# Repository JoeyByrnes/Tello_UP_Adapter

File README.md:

# Tello_UP_Adapter
hardware design files for UP Xtreme port adapter for Tello Robot

<br>

<br>

<br>

<br>

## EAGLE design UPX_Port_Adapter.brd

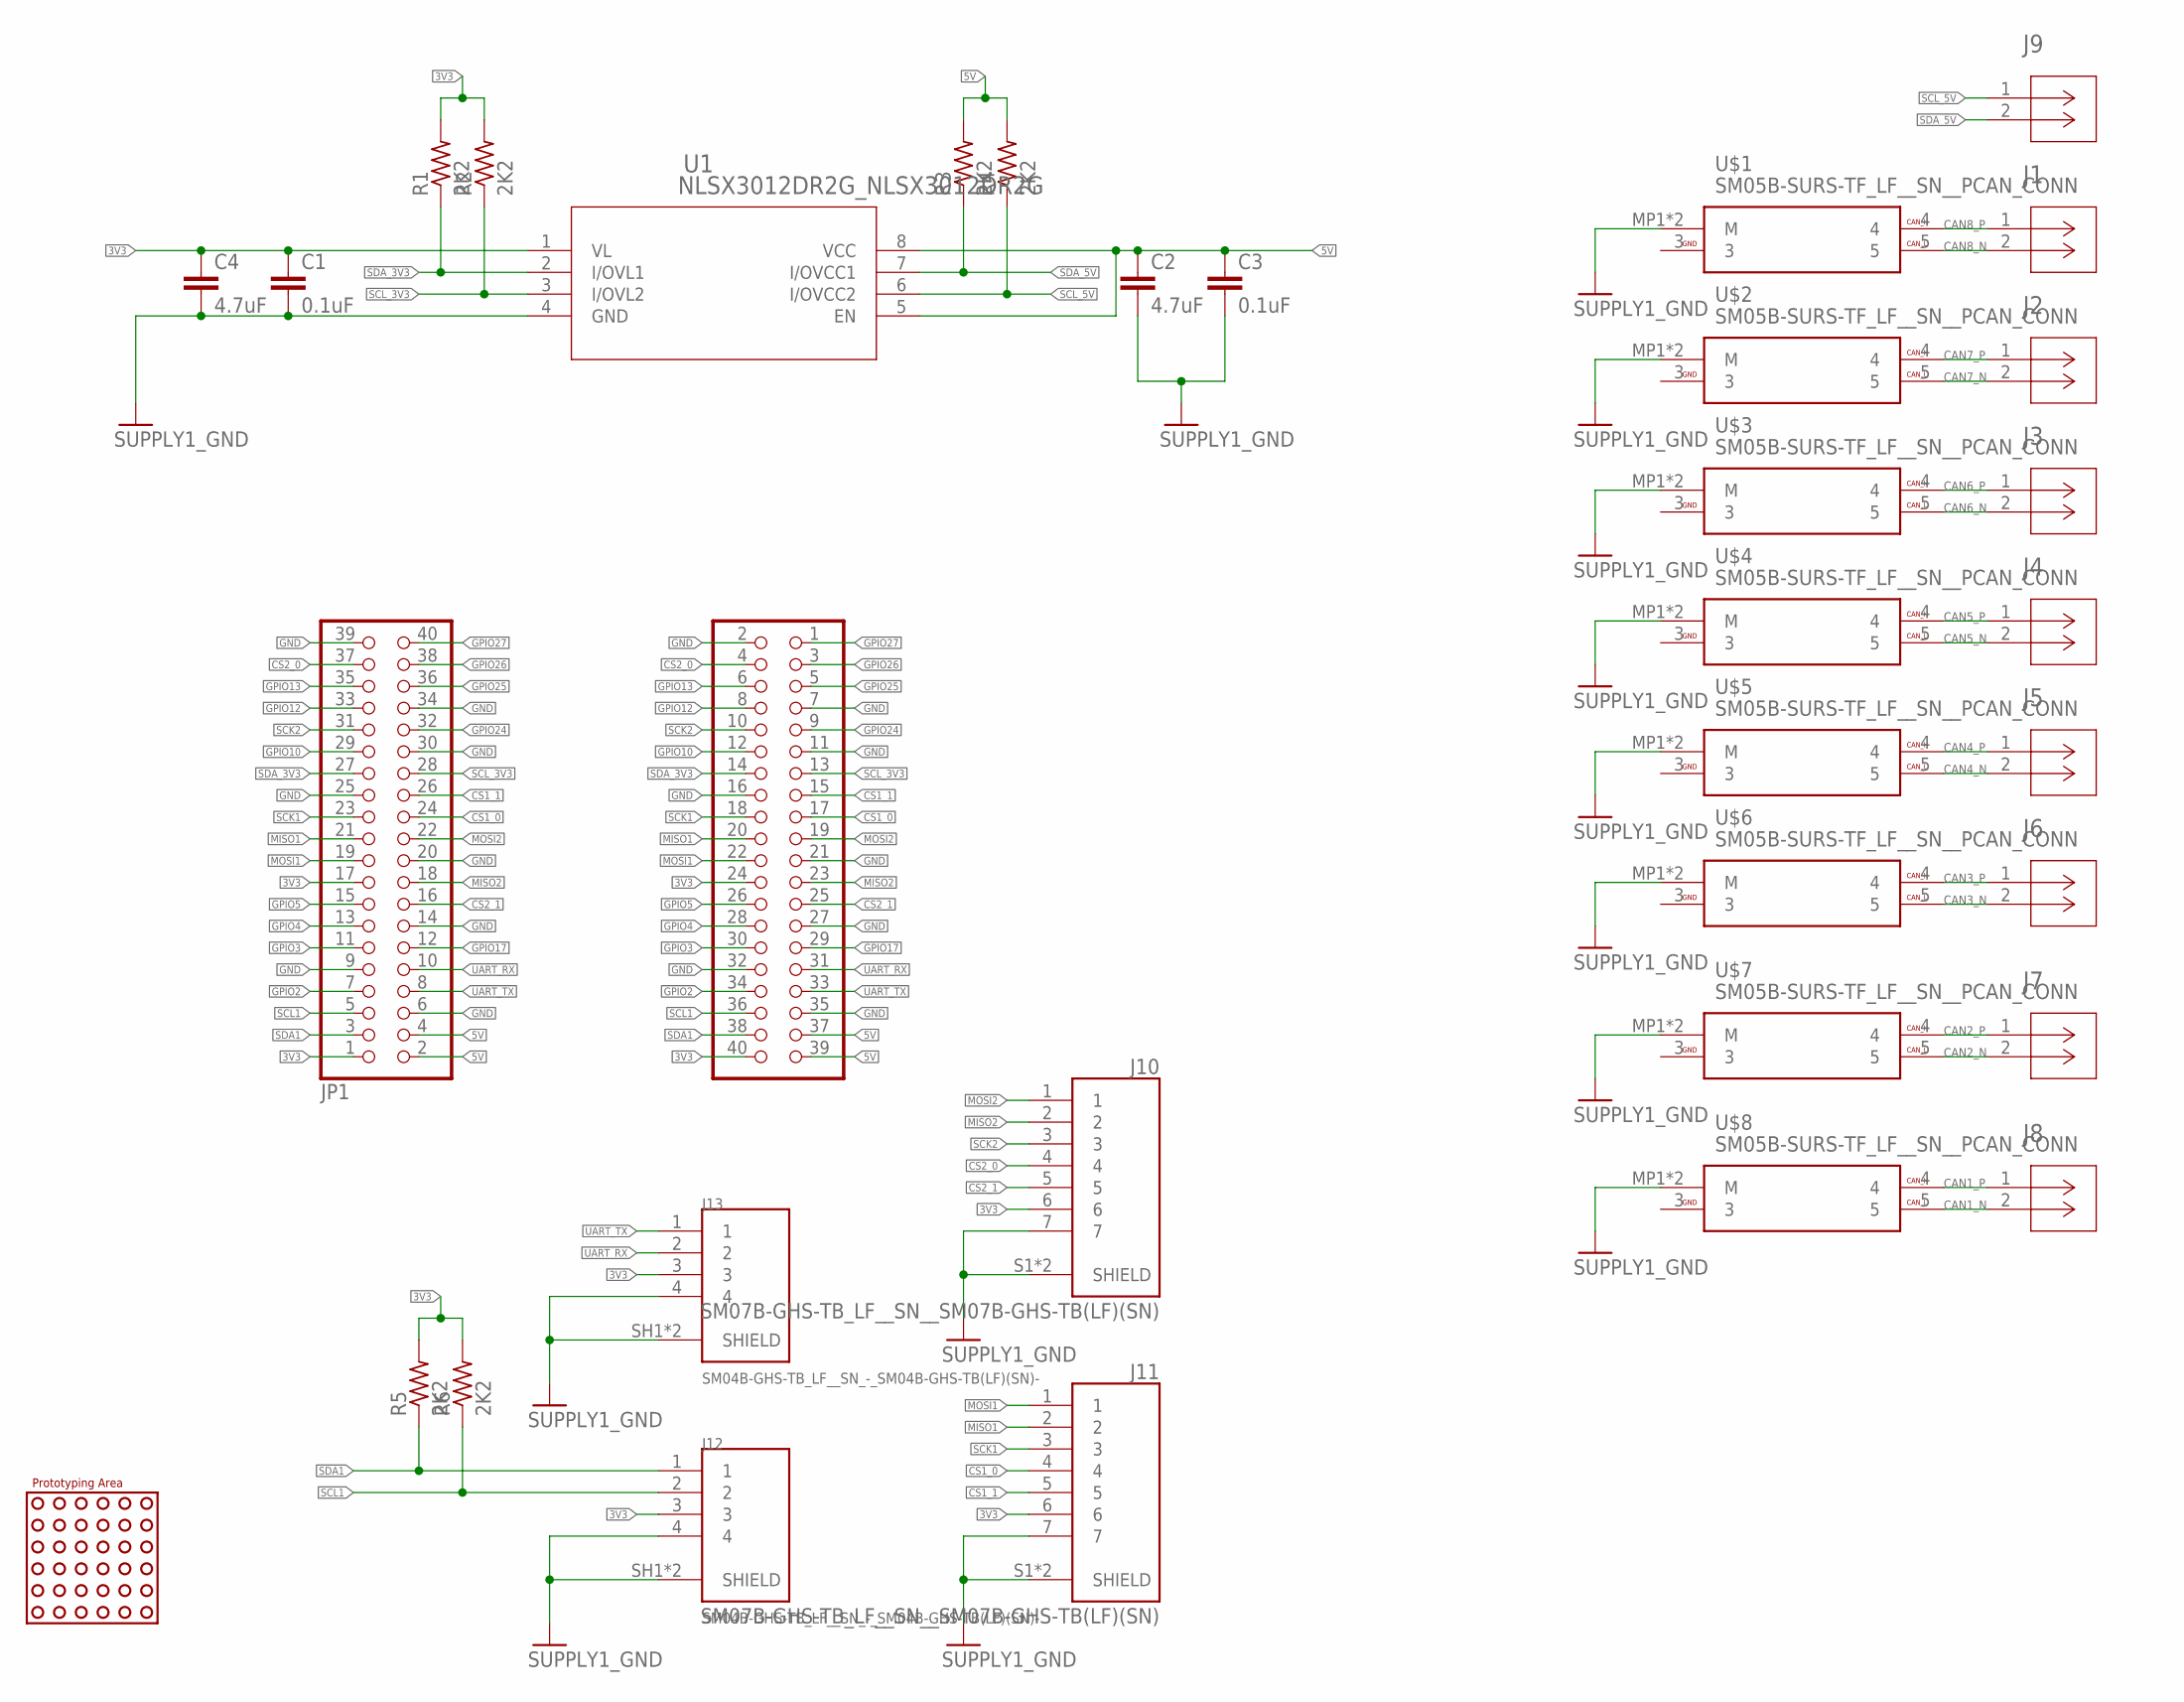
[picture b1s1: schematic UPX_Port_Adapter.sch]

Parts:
C1, C3: 0.1uF; RCL_C0603
C2, C4: 4.7uF; RCL_C0603
J1, J2, J3, J4, J5, J6, J7, J8, J9: SM02B-GHS-TB_SM02BGHSTBLFSN; SM02B-GHS-TB_CONN_SM02BGHSTB_JST
J10, J11: SM07B-GHS-TB_LF__SN__SM07B-GHS-TB(LF)(SN); SM07B-GHS-TB_LF__SN__JST_SM07B-GHS-TB(LF)(SN)
J12, J13: SM04B-GHS-TB_LF__SN_-_SM04B-GHS-TB(LF)(SN)-; SM04B-GHS-TB_LF__SN_-_JST_SM04B-GHS-TB(LF)(SN)-
JP1: PINHEAD_PINHD-2X20; PINHEAD_2X20
JP2: PINHEAD2_PINHD-2X20/90:1; PINHEAD2_2X20/90
R1, R2, R3, R4, R5, R6: 2K2; RCL_R0603
U1: NLSX3012DR2G_NLSX3012DR2G; NLSX3012DR2G_SOIC-8_NB_ONS
U$1, U$2, U$3, U$4, U$5, U$6, U$7, U$8: SM05B-SURS-TF_LF__SN__PCAN_CONN; SM05B-SURS-TF_LF__SN__SM05BSURSTFLFSN
U$9: PINHEAD-CUSTOM_20X20

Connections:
3V3: C1.1, C4.1, J10.6, J11.6, J12.3, J13.3, JP1.1, JP1.17, JP2.24, JP2.40, R1.2, R2.2, R5.2, R6.2, U1.1 (VL)
5V: C2.1, C3.1, JP1.2, JP1.4, JP2.37, JP2.39, R3.2, R4.2, U1.5 (EN), U1.8 (VCC)
CAN1_N: J8.2, U$8.5
CAN1_P: J8.1, U$8.4
CAN2_N: J7.2, U$7.5
CAN2_P: J7.1, U$7.4
CAN3_N: J6.2, U$6.5
CAN3_P: J6.1, U$6.4
CAN4_N: J5.2, U$5.5
CAN4_P: J5.1, U$5.4
CAN5_N: J4.2, U$4.5
CAN5_P: J4.1, U$4.4
CAN6_N: J3.2, U$3.5
CAN6_P: J3.1, U$3.4
CAN7_N: J2.2, U$2.5
CAN7_P: J2.1, U$2.4
CAN8_N: J1.2, U$1.5
CAN8_P: J1.1, U$1.4
CS1_0: J11.4, JP1.24, JP2.17
CS1_1: J11.5, JP1.26, JP2.15
CS2_0: J10.4, JP1.37, JP2.4
CS2_1: J10.5, JP1.16, JP2.25
GND: C1.2, C2.2, C3.2, C4.2, J10.7, J10.S1 (SHIELD), J10.S2 (SHIELD), J11.7, J11.S1 (SHIELD), J11.S2 (SHIELD), J12.4, J12.SH1 (SHIELD), J12.SH2 (SHIELD), J13.4, J13.SH1 (SHIELD), J13.SH2 (SHIELD), JP1.6, JP1.9, JP1.14, JP1.20, JP1.25, JP1.30, JP1.34, JP1.39, JP2.2, JP2.7, JP2.11, JP2.16, JP2.21, JP2.27, JP2.32, JP2.35, U1.4 (GND), U$1.MP1 (M), U$1.MP2 (M), U$2.MP1 (M), U$2.MP2 (M), U$3.MP1 (M), U$3.MP2 (M), U$4.MP1 (M), U$4.MP2 (M), U$5.MP1 (M), U$5.MP2 (M), U$6.MP1 (M), U$6.MP2 (M), U$7.MP1 (M), U$7.MP2 (M), U$8.MP1 (M), U$8.MP2 (M)
GPIO2: JP1.7, JP2.34
GPIO3: JP1.11, JP2.30
GPIO4: JP1.13, JP2.28
GPIO5: JP1.15, JP2.26
GPIO10: JP1.29, JP2.12
GPIO12: JP1.33, JP2.8
GPIO13: JP1.35, JP2.6
GPIO17: JP1.12, JP2.29
GPIO24: JP1.32, JP2.9
GPIO25: JP1.36, JP2.5
GPIO26: JP1.38, JP2.3
GPIO27: JP1.40, JP2.1
MISO1: J11.2, JP1.21, JP2.20
MISO2: J10.2, JP1.18, JP2.23
MOSI1: J11.1, JP1.19, JP2.22
MOSI2: J10.1, JP1.22, JP2.19
SCK1: J11.3, JP1.23, JP2.18
SCK2: J10.3, JP1.31, JP2.10
SCL1: J12.2, JP1.5, JP2.36, R6.1
SCL_3V3: JP1.28, JP2.13, R2.1, U1.3 (I/OVL2)
SCL_5V: J9.1, R4.1, U1.6 (I/OVCC2)
SDA1: J12.1, JP1.3, JP2.38, R5.1
SDA_3V3: JP1.27, JP2.14, R1.1, U1.2 (I/OVL1)
SDA_5V: J9.2, R3.1, U1.7 (I/OVCC1)
UART_RX: J13.2, JP1.10, JP2.31
UART_TX: J13.1, JP1.8, JP2.33

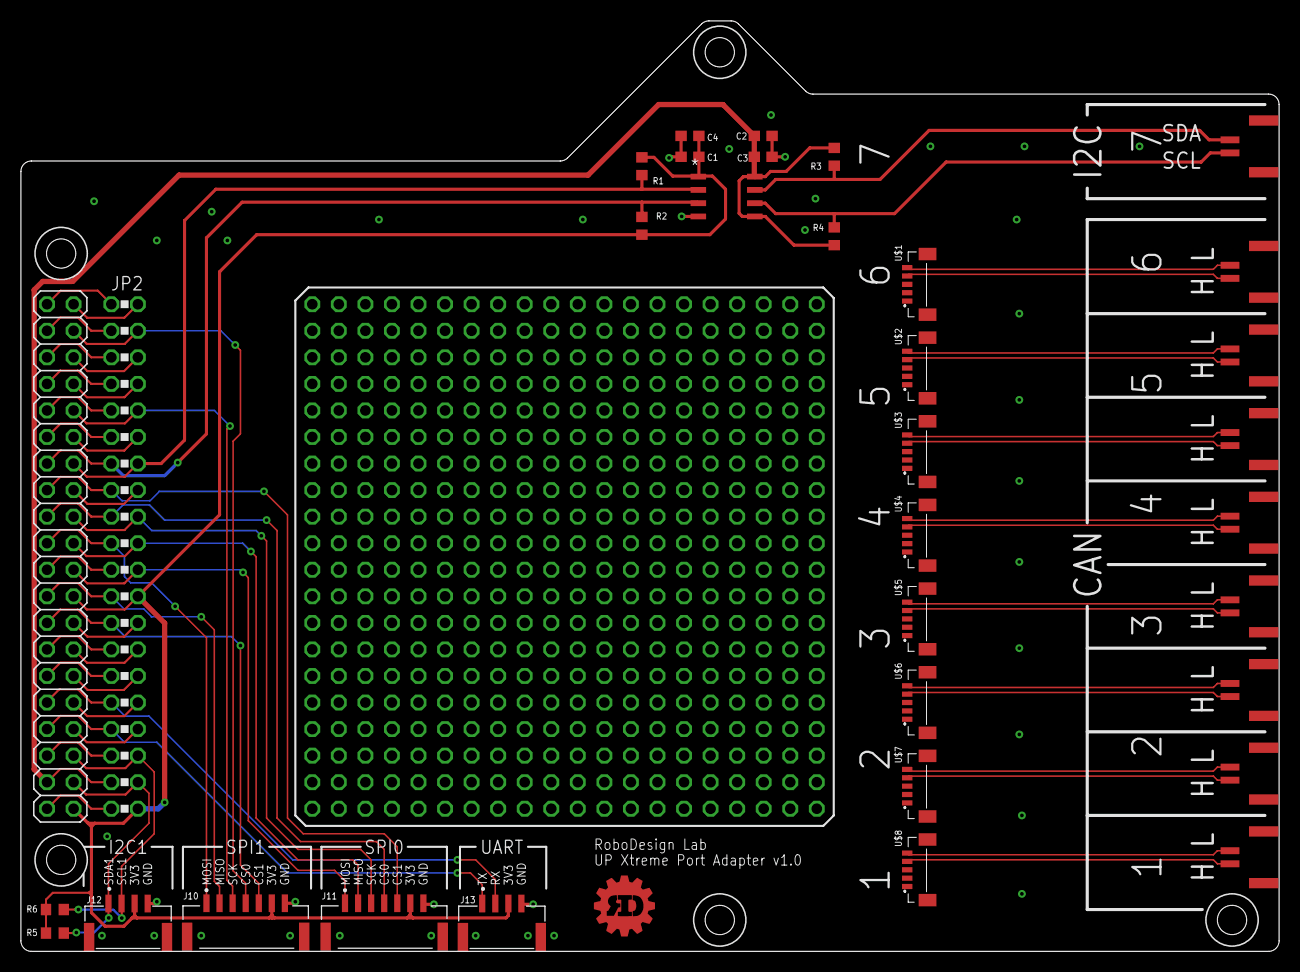
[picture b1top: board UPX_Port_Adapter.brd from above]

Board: 4 copper layers, 120.3 x 89.0 mm, 35 parts (0 on the bottom side), 49 nets.

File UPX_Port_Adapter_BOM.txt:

Partlist exported from C:/Users/joeyb/Documents/Github/RoboDesignLab/Tello_UP_Adapter/UPX_Port_Adapter.sch at 11/12/2022 7:18 AM

Qty Value                                       Device                                      Package                                         Parts                                  Description                                              COPYRIGHT                                                DESCRIPTION                                                             DIGI-KEY_PART_NUMBER DIGI-KEY_PART_NUMBER_1  DIGI-KEY_PART_NUMBER_2 DIGI-KEY_PART_NUMBER_3 DIGI-KEY_PART_NUMBER_4 DIGI-KEY_PART_NUMBER_5 MANUFACTURER_PART_NUMBER MF        MFR_NAME MP                    PACKAGE POPULARITY PURCHASE-URL                                                           SPICEPREFIX
-----------------------------------------------1                                               PINHEAD2_PINHD-2X20/90:1                    PINHEAD2_2X20/90                                JP2                                    PIN HEADER                                                                                                                                                                                                                                                                                                                                                                                                   0                                                                                            
-----------------------------------------------1                                               PINHEAD_PINHD-2X20                          PINHEAD_2X20                                    JP1                                    PIN HEADER                                                                                                                                                                                                                                                                                                                                                                                                   0                                                                                            
-----------------------------------------------2   0.1uF                                       RCL_C-EUC0603                               RCL_C0603                                       C1, C3                                 CAPACITOR, European symbol                                                                                                                                                                                                                                                                                                                                                                                   0                                                                                 C          
-----------------------------------------------6   2K2                                         RCL_R-US_R0603                              RCL_R0603                                       R1, R2, R3, R4, R5, R6                 RESISTOR, American symbol                                                                                                                                                                                                                                                                                                                                                                                    0                                                                                 R          
-----------------------------------------------2   4.7uF                                       RCL_C-EUC0603                               RCL_C0603                                       C2, C4                                 CAPACITOR, European symbol                                                                                                                                                                                                                                                                                                                                                                                   0                                                                                 C          
-----------------------------------------------1   NLSX3012DR2G_NLSX3012DR2G                   NLSX3012DR2G_NLSX3012DR2G                   NLSX3012DR2G_SOIC-8_NB_ONS                      U1                                                                                              Copyright (C) 2022 Ultra Librarian. All rights reserved.                                                                                              2156-NLSX3012DR2G-OS-ND NLSX3012DR2G-ND        NLSX3012DR2GOSCT-ND    NLSX3012DR2GOSDKR-ND   NLSX3012DR2GOSTR-ND    NLSX3012DR2G                       onsemi                                                                                                                              
-----------------------------------------------9   SM02B-GHS-TB_SM02BGHSTBLFSN                 SM02B-GHS-TB_SM02BGHSTBLFSN                 SM02B-GHS-TB_CONN_SM02BGHSTB_JST                J1, J2, J3, J4, J5, J6, J7, J8, J9                                                              Copyright (C) 2022 Ultra Librarian. All rights reserved.                                                                                              455-1564-2-ND           455-1564-1-ND          455-1564-6-ND                                                        SM02BGHSTBLFSN                     JST                                                                                                                                 
------2   SM04B-GHS-TB_LF__SN_-_SM04B-GHS-TB(LF)(SN)- SM04B-GHS-TB_LF__SN_-_SM04B-GHS-TB(LF)(SN)- SM04B-GHS-TB_LF__SN_-_JST_SM04B-GHS-TB(LF)(SN)- J12, J13                               Conn Header Gh Side 4pos 1.25mm                                                                                    Connector Header Surface Mount, Right Angle 4 position 0.049 (1.25mm)  455-1566-2-ND                                                                                                                                                     JST Sales          SM04B-GHS-TB(LF)(SN)- None               https://pricing.snapeda.com/search/part/SM04B-GHS-TB(LF)(SN)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            
FOUND ALTERNATIVE VERTICAL CONNECTOR-----------8   SM05B-SURS-TF_LF__SN__PCAN_CONN             SM05B-SURS-TF_LF__SN__PCAN_CONN             SM05B-SURS-TF_LF__SN__SM05BSURSTFLFSN           U$1, U$2, U$3, U$4, U$5, U$6, U$7, U$8                                                                                                                                                                                                                                                                                                                                                                                                                                                                                                           
-----------------------------------------------2   SM07B-GHS-TB_LF__SN__SM07B-GHS-TB(LF)(SN)   SM07B-GHS-TB_LF__SN__SM07B-GHS-TB(LF)(SN)   SM07B-GHS-TB_LF__SN__JST_SM07B-GHS-TB(LF)(SN)   J10, J11                               Conn Shrouded Header HDR 7 POS 1.25mm Solder RA SMD Reel                                                           Connector Header Surface Mount, Right Angle 7 position 0.049 (1.25mm)  455-1569-2-ND                                                                                                                                                     JST Sales          SM07B-GHS-TB(LF)(SN)  None               https://pricing.snapeda.com/search/part/SM07B-GHS-TB(LF)(SN)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

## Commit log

2022-09-27 finished routing v1
2022-09-27 Traces Reviewed
2022-09-28 Added mfg files and visuals
2023-10-02 added manufacturing files, edited readme

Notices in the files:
parts and their libraries:
COPYRIGHT: Copyright (C) 2022 Ultra Librarian. All rights reserved.
